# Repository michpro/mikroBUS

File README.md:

# mikroBUS™ Add-on Boards Collection

This repository contains a collection of add-on boards designed according to the mikroBUS™ standard. These boards can be used with any microcontroller platform that supports the mikroBUS™ socket, providing an easy way to expand the functionality of your projects.

* [**BluePill Base Board with 3 MikroBUS Sockets**](/BluePill_base/README.md)
* [**Arduino UNO Click Shield**](/Arduino_UNO_click_shield/README.md) -  SPI to UART firmware

---

* [**CAN Click**](/CAN_Click/README.md)
* [**Ethernet W5500 mini Click**](/ETH_W5500_mini_Click/README.md)
* [**HLW8032 Click - energy metering module**](/HLW8032_Click/README.md)
* [**I²C to 1-Wire Click**](/I2C_1-Wire_Click/README.md)
* [**I²C EEPROM/FRAM Click**](/I2C_EEPROM_Click/README.md)
* [**LIN Click**](/LIN_Click/README.md)
* [**LoRa Click**](/LoRa_Click/README.md)
* [**OpenTherm Click**](/OpenTherm_Click/README.md)
* [**RS485 Click**](/RS485_Click/README.md)
* [**UI Click with SCT-013 interface**](/SCT-013_UI_Click/README.md)

## **Reporting bugs**

[Create an issue on GitHub](https://github.com/michpro/mikroBUS/issues)

---

## **License**

Copyright © 2023-2025 Michal Protasowicki

This project is released under CERN Open Hardware Licence Version 2 - Permissive.

The software parts of the project are available under the MIT licence.

---

## **Support**
If You find my projects interesting and You wanted to support my work, You can give me a cup of coffee or a keg of beer :)

&nbsp;&nbsp;&nbsp;&nbsp;&nbsp;&nbsp;&nbsp;&nbsp;&nbsp;&nbsp;

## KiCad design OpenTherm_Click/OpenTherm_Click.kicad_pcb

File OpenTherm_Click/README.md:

# **OpenTherm Click**

- [**OpenTherm Click**](#opentherm-click)
  - [**Overview**](#overview)
    - [**Features**](#features)
  - [**Schematic diagram**](#schematic-diagram)
  - [**Module visualisation**](#module-visualisation)
  - [**Assembly**](#assembly)
  - [**Production files**](#production-files)
  - [**Testing out the hardware**](#testing-out-the-hardware)
    - [Prerequisites](#prerequisites)
    - [Instructions](#instructions)
    - [Notes](#notes)
  - [**Software**](#software)
  - [**Reporting bugs**](#reporting-bugs)
  - [**License**](#license)
    - [**Hardware**](#hardware)
    - [**Software**](#software-1)
  - [**Support**](#support)

---

## **Overview**
The OpenTherm Click is a compact module designed to interface with OpenTherm-compatible heating systems, such as boilers and thermostats. It facilitates communication using the OpenTherm protocol, incorporating electrical isolation for safety and compatibility.

### **Features**
* OpenTherm slave interface to communicate with a boiler
* OpenTherm master interface to communicate with a thermostat
* can implement master, slave and gateway modes
* built-in (3.3-5V) to 24V DC-DC step up converter
* Compact Design - optimized for integration with microcontroller systems, such as mikroBUS™ Click boards.

This work is based on [otgw.tclcode.com](https://otgw.tclcode.com) project.

---

## **Schematic diagram**

## **Module visualisation**
(click on the image to see the 3D model)
<p align="center"></p>

## **Assembly**
[Interactive BOM and placement](https://michpro.github.io/mikroBUS/OpenTherm_Click/docs/ibom.html)

## **Production files**
Production files can be found [**here**](./production/).

---
## **Testing out the hardware**
Below are the start-up instructions for the [click_test.ino](./software/click_test/click_test.ino) Arduino program, a diagnostic tool designed to test and validate the electrical and communication integrity between a boiler and thermostat circuits on the OpenTherm Click. These instructions guide you through the process step-by-step, ensuring you can verify your hardware setup correctly.

### Prerequisites
- **OpenTherm Click**: Ensure it is properly connected to base µC module.
- **Computer**: Equipped with Arduino IDE or a serial monitor software.
- **Multimeter**: Required for measuring voltages and currents.
- **Two Wires**: Needed to connect the BOILER and THERM terminals during testing.

### Instructions

1. **Upload the Program**
   - Load the [click_test.ino](./software/click_test/click_test.ino) program onto your Arduino board using the Arduino IDE.<br>
    *If necessary, adjust the pins used in the programme.*

2. **Open Serial Monitor**
   - Launch the serial monitor in the Arduino IDE or your preferred serial terminal software.
   - Set the baud rate to **115200**.

3. **Initial Setup**
   - Disconnect the 'THERM' and 'BOILER' terminals from each other if they are connected.
   - Check the LEDs on the Click:
     - **'PWR'** and **'RxT'** LEDs should be lit.
     - **'RxB'** LED should be off.
   - The serial monitor will display a prompt. If the LED statuses match, type **`y`** and press Enter to proceed.

4. **Voltage Measurement 1**
   - Use a multimeter to measure the voltage between the **+24V test point** and **GND**.
   - Expected range: **23.5V to 24.5V**.
   - If within range, type **`y`** in the serial monitor to proceed.

5. **Voltage Measurement 2**
   - Measure the voltage between the **T+ test point** and **GND**.
   - Expected value: Approximately **24V**.
   - If correct, type **`y`** to proceed.

6. **Current Measurement 1**
   - Measure the current flowing between **T+** and **GND**.
   - Expected range: **5mA to 9mA**.
   - Verify that the **RxT LED** is **not lit** during this measurement.
   - If correct, type **`y`** to proceed.

7. **Activate MASTER-OUT and Current Measurement 2**
   - The program will activate the 'MASTER-OUT' line (you’ll see a message in the serial monitor).
   - Measure the current between **T+** and **GND** again.
   - Expected range: **17mA to 23mA**.
   - Ensure the **RxT LED** remains **not lit**.
   - If correct, type **`y`** to proceed.

8. **Connect Terminals and Voltage Measurement 3**
   - Connect the **BOILER** and **THERM** terminals using two wires (polarity does not matter).
   - Measure the voltage between test points **B1** and **B2**.
   - Expected range: **15V to 18V**.
   - If within range, type **`y`** to proceed.

9. **Check RxB LED**
   - The program will activate 'MASTER-OUT' again.
   - Observe the **'RxB' LED**; it should **light up**.
   - If it does, type **`y`** to proceed.

10. **Activate SLAVE-OUT and Voltage Measurement 4**
    - The program will activate the 'SLAVE-OUT' line.
    - Check that the **RxT LED** **stops lighting up**.
    - Measure the voltage between **B1** and **B2** again.
    - Expected range: **5V to 7V**.
    - If correct, type **`y`** to proceed.

11. **Test Result**
    - If all steps are completed successfully, the serial monitor will display:
      ```
      *****************
      *  TEST PASSED  *
      *****************
      ```
    - If any step fails, it will show:
      ```
      *****************
      * TEST FAIL !!! *
      *****************
      ```

12. **Continuous Testing (if passed)**
    - If the test passes, the program will enter a continuous testing mode.
    - It will repeatedly check communication between the boiler and thermostat, printing:
      - **"Boiler inbound, thermostat outbound ... OK"** or **"Failed"** with a reason.
      - **"Boiler outbound, thermostat inbound ... OK"** or **"Failed"** with a reason.

### Notes
- **Test Points and LEDs**: Ensure you correctly identify the test points (+24V, T+, GND, B1, B2) and LEDs (PWR, RxT, RxB) on the OpenTherm Click.
- **Safety**: Exercise caution when measuring voltages and currents to avoid short circuits.
- **Troubleshooting**: If a measurement falls outside the expected range:
  - Double-check your connections and multimeter settings.
  - Retry the step. Persistent issues may indicate a problem with the Click or setup.

<br>

***Follow these instructions carefully to test and validate your OpenTherm Click setup. Each step requires confirmation via the serial monitor, so keep it open and active throughout the process. Successful completion ensures your boiler and thermostat circuits are functioning correctly.***

---

## **Software**
- Recommended library for use in your OpenTherm projects: 
  [https://github.com/ihormelnyk/opentherm_library](https://github.com/ihormelnyk/opentherm_library)

---

## **Reporting bugs**

[Create an issue on GitHub](https://github.com/michpro/mikroBUS/issues)

---

## **License**
Copyright © 2025 Michal Protasowicki

### **Hardware**
  * Hardware part of this project is released under CERN Open Hardware Licence Version 2 - Permissive.

### **Software**
  * Software part of this project is released under MIT Licence.

---

## **Support**
If You find my projects interesting and You wanted to support my work, You can give me a cup of coffee or a keg of beer :)

&nbsp;&nbsp;&nbsp;&nbsp;&nbsp;&nbsp;&nbsp;&nbsp;&nbsp;&nbsp;

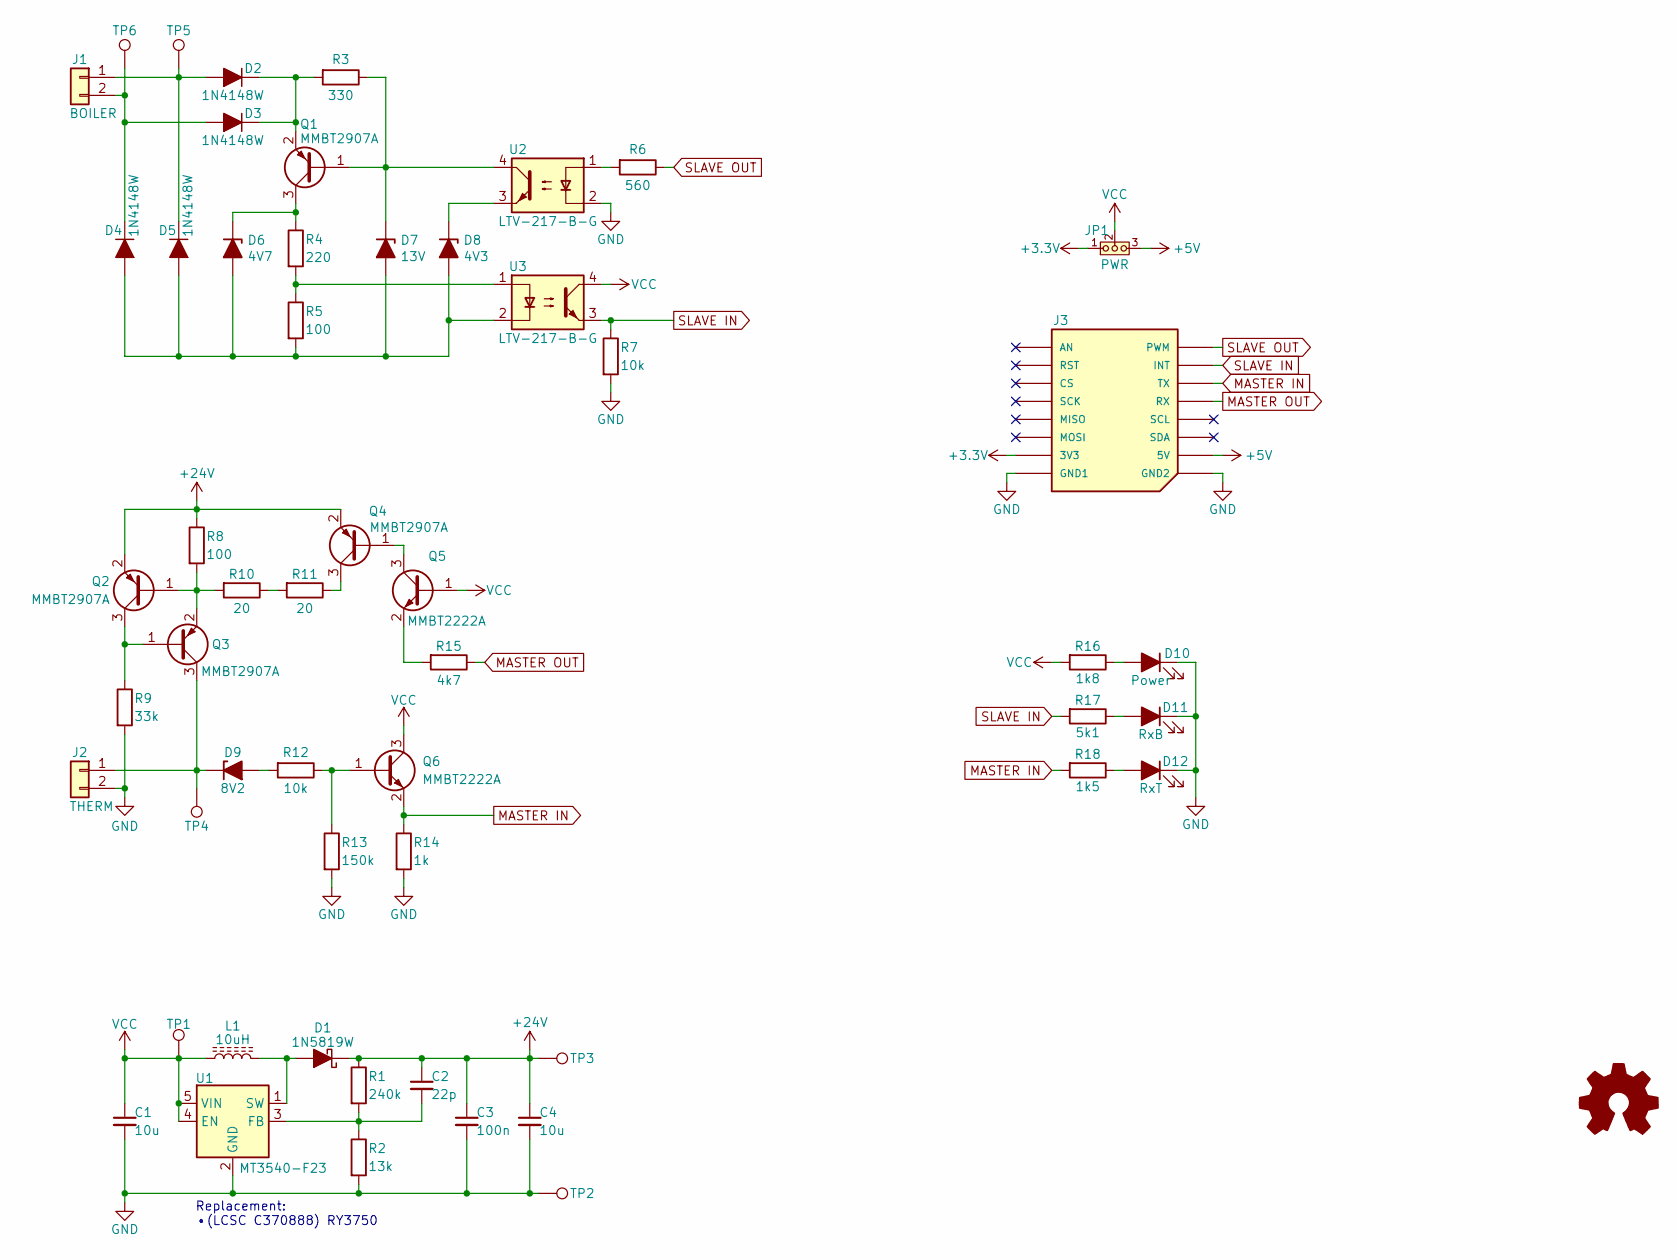
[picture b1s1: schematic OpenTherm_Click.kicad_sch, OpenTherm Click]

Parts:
C1: 10u; C_0603_1608Metric; LCSC C19702
C2: 22p; C_0603_1608Metric; LCSC C1653
C3: 100n; C_0603_1608Metric; LCSC C14663
C4: 10u; C_0805_2012Metric; LCSC C440198
D1: 1N5819W; D_SOD-123; LCSC C8598
D2, D3, D4, D5: 1N4148W; D_SOD-123; LCSC C7420318
D6: 4V7; D_SOD-123; LCSC C19077400
D7: 13V; D_SOD-123; LCSC C22399883
D8: 4V3; D_SOD-123; LCSC C19077399
D9: 8V2; D_SOD-123; LCSC C22399882
D10: Power; LED_0805_2012Metric; LCSC C84256
D11: RxB; LED_0805_2012Metric; LCSC C2297
D12: RxT; LED_0805_2012Metric; LCSC C2296
J1: BOILER; Altech_AK100_1x02_P5.00mm; LCSC ------
J2: THERM; Altech_AK100_1x02_P5.00mm; LCSC ------
J3: OpenTherm Click v${REVISION} by MPro; mikroBUS_module_L; LCSC -----
JP1: PWR; PinHeader_1x03_P2.54mm_Vertical; LCSC C5383112
L1: 10uH; Inductor_4.2x4.4mm; LCSC C177242
LOGO1: Logo_Open_Hardware_Small; OSHW-Logo2_7.3x6mm_SilkScreen
Q1, Q2, Q3, Q4: MMBT2907A; SOT-23; LCSC C7420352
Q5, Q6: MMBT2222A; SOT-23; LCSC C8512
R1: 240k; R_0603_1608Metric; LCSC C4197
R2: 13k; R_0603_1608Metric; LCSC C22797
R3: 330; R_0603_1608Metric; LCSC C23138
R4: 220; R_0603_1608Metric; LCSC C22962
R5, R8: 100; R_0603_1608Metric; LCSC C22775
R6: 560; R_0603_1608Metric; LCSC C23204
R7, R12: 10k; R_0603_1608Metric; LCSC C25804
R9: 33k; R_0603_1608Metric; LCSC C4216
R10, R11: 20; R_0603_1608Metric; LCSC C22950
R13: 150k; R_0603_1608Metric; LCSC C22807
R14: 1k; R_0603_1608Metric; LCSC C21190
R15: 4k7; R_0603_1608Metric; LCSC C23162
R16: 1k8; R_0603_1608Metric; LCSC C4177
R17: 5k1; R_0603_1608Metric; LCSC C23186
R18: 1k5; R_0603_1608Metric; LCSC C22843
TP1: VCC; TestPoint_Pad_D2.0mm; LCSC ------
TP2: GND; TestPoint_Pad_D2.0mm; LCSC ------
TP3: +24V; TestPoint_Pad_D2.0mm; LCSC ------
TP4: T+; TestPoint_Pad_D2.0mm; LCSC ------
TP5: B1; TestPoint_Pad_D2.0mm; LCSC ------
TP6: B2; TestPoint_Pad_D2.0mm; LCSC ------
U1: MT3540-F23; SOT-23-5; LCSC C181783
U2, U3: LTV-217-B-G; SOP-4_4.4x2.6mm_P1.27mm; LCSC C115450

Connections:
+3.3V: J3.P7 (3V3), JP1.1 (A)
+5V: J3.P10 (5V), JP1.3 (B)
+24V: C2.1, C3.1, C4.1, D1.1 (K), Q2.2 (E), Q4.2 (E), R1.1, R8.1, TP3.1
GND: C1.2, C3.2, C4.2, D10.1 (K), D11.1 (K), D12.1 (K), J2.2, J3.P8 (GND1), J3.P9 (GND2), R2.2, R7.2, R9.2, R13.2, R14.2, TP2.1, U1.2 (GND), U2.2
MASTER IN: J3.P14 (TX), Q6.2 (E), R14.1, R18.2
MASTER OUT: J3.P13 (RX), R15.1
unnamed: D1.2 (A), L1.2, U1.1 (SW)
unnamed: D2.2 (A), D5.1 (K), J1.1, TP5.1
unnamed: D2.1 (K), D3.1 (K), Q1.2 (E), R3.2
unnamed: D3.2 (A), D4.1 (K), J1.2, TP6.1
unnamed: D4.2 (A), D5.2 (A), D6.2 (A), D7.2 (A), D8.2 (A), R5.2, U3.2
unnamed: D6.1 (K), Q1.3 (C), R4.1
unnamed: D7.1 (K), Q1.1 (B), R3.1, U2.4
unnamed: D8.1 (K), U2.3
unnamed: D9.2 (A), R12.2
unnamed: D9.1 (K), J2.1, Q3.3 (C), TP4.1
unnamed: D10.2 (A), R16.1
unnamed: D11.2 (A), R17.1
unnamed: D12.2 (A), R18.1
unnamed: Q2.1 (B), Q3.2 (E), R8.2, R10.2
unnamed: Q2.3 (C), Q3.1 (B), R9.1
unnamed: Q4.1 (B), Q5.3 (C)
unnamed: Q4.3 (C), R11.1
unnamed: Q5.2 (E), R15.2
unnamed: Q6.1 (B), R12.1, R13.1
unnamed: R4.2, R5.1, U3.1
unnamed: R6.2, U2.1
unnamed: R10.1, R11.2
unnamed: C2.2, R1.2, R2.1, U1.3 (FB)
SLAVE IN: J3.P15 (INT), R7.1, R17.2, U3.3
SLAVE OUT: J3.P16 (PWM), R6.1
VCC: C1.1, JP1.2 (C), L1.1, Q5.1 (B), Q6.3 (C), R16.2, TP1.1, U1.4 (EN), U1.5 (VIN), U3.4

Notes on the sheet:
Replacement: •(LCSC C370888) RY3750

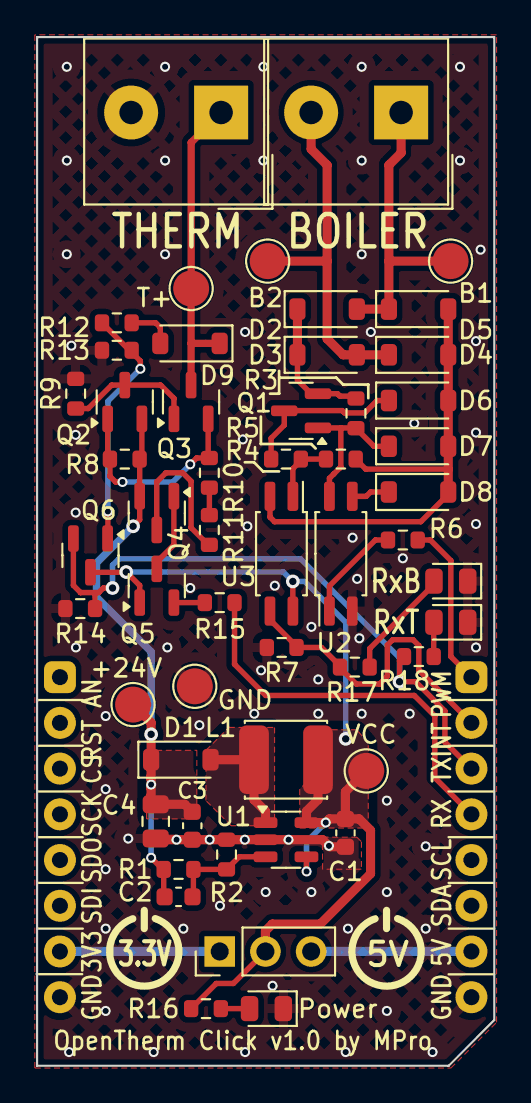
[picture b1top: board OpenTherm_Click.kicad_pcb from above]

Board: 2 copper layers, 25.4 x 57.2 mm, 55 parts (1 on the bottom side), 32 nets.

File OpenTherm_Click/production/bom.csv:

Designator,Footprint,Quantity,Value,LCSC Part #
C1,0603,1,10u,C19702
C2,0603,1,22p,C1653
C3,0603,1,100n,C14663
C4,0805,1,10u,C440198
D1,D_SOD-123,1,1N5819W,C8598
D10,0805,1,Power,C84256
D11,0805,1,RxB,C2297
D12,0805,1,RxT,C2296
"D2, D3, D4, D5",D_SOD-123,4,1N4148W,C7420318
D6,D_SOD-123,1,4V7,C19077400
D7,D_SOD-123,1,13V,C22399883
D8,D_SOD-123,1,4V3,C19077399
D9,D_SOD-123,1,8V2,C22399882
JP1,PinHeader_1x03_P2.54mm_Vertical,1,PWR,C5383112
L1,Inductor_4.2x4.4mm,1,10uH,C177242
"Q1, Q2, Q3, Q4",SOT-23,4,MMBT2907A,C7420352
"Q5, Q6",SOT-23,2,MMBT2222A,C8512
R1,0603,1,240k,C4197
"R10, R11",0603,2,20,C22950
"R12, R7",0603,2,10k,C25804
R13,0603,1,150k,C22807
R14,0603,1,1k,C21190
R15,0603,1,4k7,C23162
R16,0603,1,1k8,C4177
R17,0603,1,5k1,C23186
R18,0603,1,1k5,C22843
R2,0603,1,13k,C22797
R3,0603,1,330,C23138
R4,0603,1,220,C22962
"R5, R8",0603,2,100,C22775
R6,0603,1,560,C23204
R9,0603,1,33k,C4216
U1,SOT-23-5,1,MT3540-F23,C181783
"U2, U3",SOP-4_4.4x2.6mm_P1.27mm,2,LTV-217-B-G,C115450

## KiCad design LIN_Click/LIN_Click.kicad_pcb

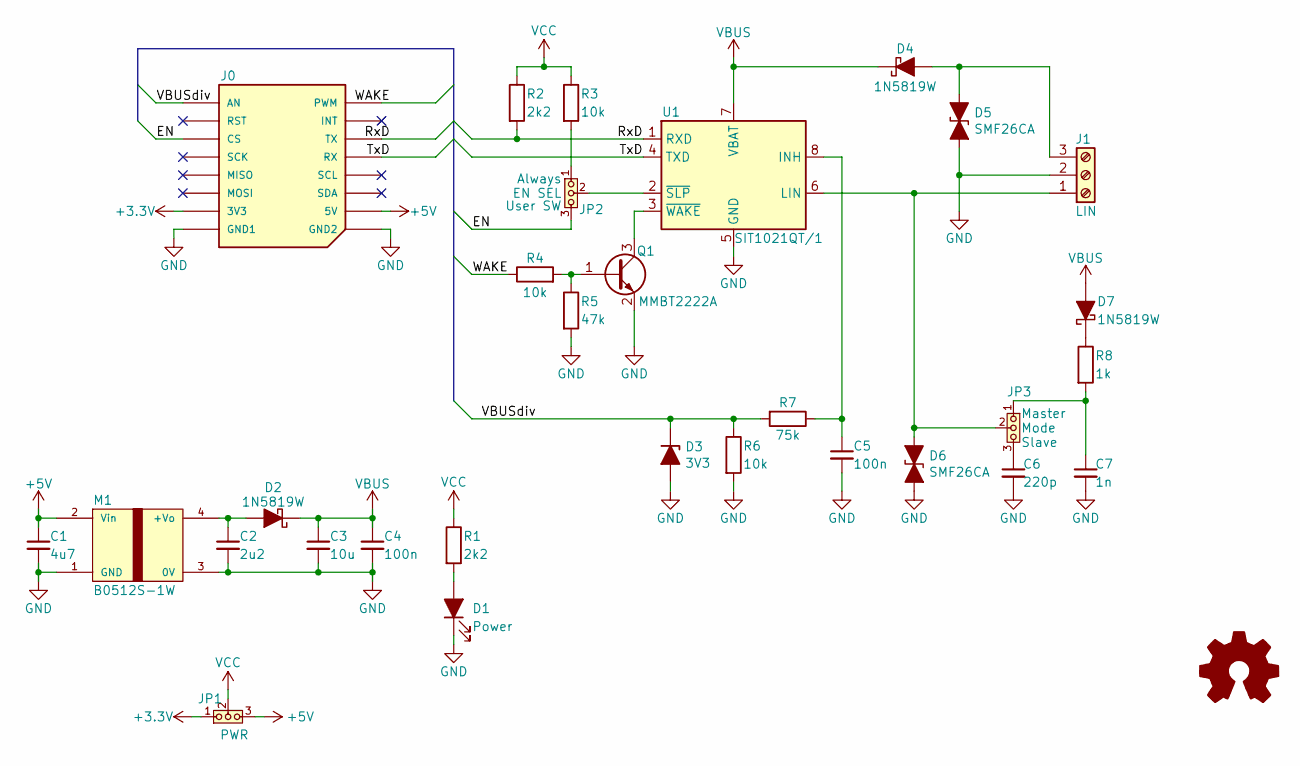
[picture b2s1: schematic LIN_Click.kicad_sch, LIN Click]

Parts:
C1: 4u7; C_0805_2012Metric; LCSC C1779
C2: 2u2; C_0805_2012Metric; LCSC C377773
C3: 10u; C_0805_2012Metric; LCSC C440198
C4, C5: 100n; C_0805_2012Metric; LCSC C49678
C6: 220p; C_0805_2012Metric; LCSC C107145
C7: 1n; C_0805_2012Metric; LCSC C46653
D1: Power; LED_0805_2012Metric; LCSC C2296
D2, D4, D7: 1N5819W; D_SOD-123; LCSC C8598
D3: 3V3; D_SOD-123; LCSC C19077392
D5, D6: SMF26CA; D_SOD-123FL; LCSC C19077516
J0: LIN Click v${REVISION} by MPro; mikroBUS_module_M; LCSC -----
J1: LIN; DG250-3.5-03P-11-00AH; LCSC -----
JP1: PWR; PinHeader_1x03_P2.54mm_Vertical; LCSC C5383112
JP2: EN SEL; PinHeader_1x03_P2.54mm_Vertical; LCSC C5383112
JP3: Mode; PinHeader_1x03_P2.54mm_Vertical; LCSC C5383112
LOGO1: Logo_Open_Hardware_Small; OSHW-Logo2_7.3x6mm_SilkScreen
M1: B0512S-1W; BxxyyS-1W; LCSC C3031179
Q1: MMBT2222A; SOT-23; LCSC C8512
R1, R2: 2k2; R_0805_2012Metric; LCSC C17520
R3, R4, R6: 10k; R_0805_2012Metric; LCSC C17414
R5: 47k; R_0805_2012Metric; LCSC C17713
R7: 75k; R_0805_2012Metric; LCSC C17819
R8: 1k; R_0805_2012Metric; LCSC C17513
U1: SIT1021QT/1; SO-8_3.9x4.9mm_P1.27mm; LCSC C7433978

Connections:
+3.3V: J0.P7 (3V3), JP1.1 (A)
+5V: C1.1, J0.P10 (5V), JP1.3 (B), M1.2 (Vin)
/EN: J0.P3 (CS), JP2.3 (B)
/RxD: J0.P14 (TX), R2.2, U1.1 (RXD)
/TxD: J0.P13 (RX), U1.4 (TXD)
/VBUSdiv: D3.1 (K), J0.P1 (AN), R6.1, R7.2
/WAKE: J0.P16 (PWM), R4.1
GND: C1.2, C2.2, C3.2, C4.2, C5.2, C6.2, C7.2, D1.1 (K), D3.2 (A), D5.2 (A2), D6.2 (A2), J0.P8 (GND1), J0.P9 (GND2), J1.2, M1.1 (GND), M1.3 (0V), Q1.2 (E), R5.2, R6.2, U1.5 (GND)
unnamed: D1.2 (A), R1.2
unnamed: C2.1, D2.2 (A), M1.4 (+Vo)
unnamed: D4.2 (A), D5.1 (A1), J1.3
unnamed: D6.1 (A1), J1.1, JP3.2 (C), U1.6 (LIN)
unnamed: D7.1 (K), R8.1
unnamed: JP2.1 (A), R3.2
unnamed: JP2.2 (C), U1.2 (~SLP)
unnamed: C7.1, JP3.1 (A), R8.2
unnamed: C6.1, JP3.3 (B)
unnamed: Q1.1 (B), R4.2, R5.1
unnamed: Q1.3 (C), U1.3 (~WAKE)
unnamed: C5.1, R7.1, U1.8 (INH)
VBUS: C3.1, C4.1, D2.1 (K), D4.1 (K), D7.2 (A), U1.7 (VBAT)
VCC: JP1.2 (C), R1.1, R2.1, R3.1

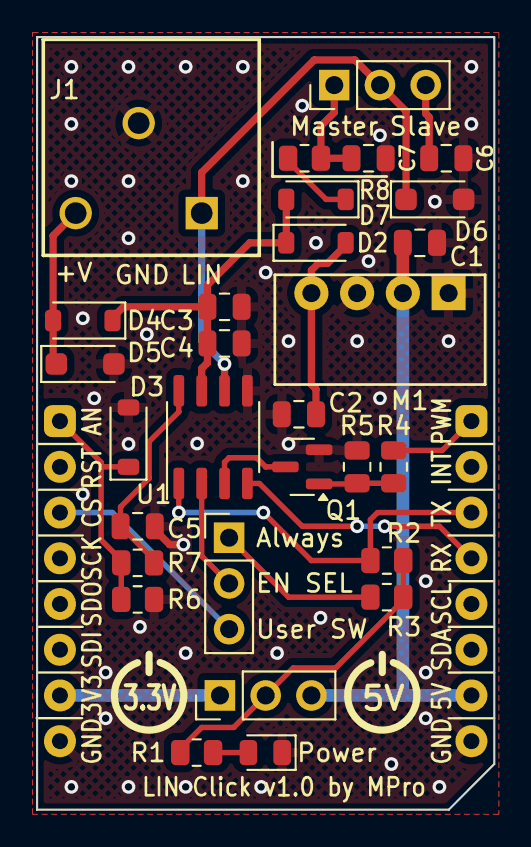
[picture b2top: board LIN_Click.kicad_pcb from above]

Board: 2 copper layers, 25.4 x 42.9 mm, 31 parts (1 on the bottom side), 22 nets.

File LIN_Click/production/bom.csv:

Designator,Footprint,Quantity,Value,LCSC Part #
C1,0805,1,4u7,C1779
C2,0805,1,2u2,C377773
C3,0805,1,10u,C440198
"C4, C5",0805,2,100n,C49678
C6,0805,1,220p,C107145
C7,0805,1,1n,C46653
D1,0805,1,Power,C2296
"D2, D4, D7",D_SOD-123,3,1N5819W,C8598
D3,D_SOD-123,1,3V3,C19077392
"D5, D6",D_SOD-123FL,2,SMF26CA,C19077516
J1,DG250-3.5-03P-11-00AH,1,LIN,-----
JP1,PinHeader_1x03_P2.54mm_Vertical,1,PWR,C5383112
JP2,PinHeader_1x03_P2.54mm_Vertical,1,EN SEL,C5383112
JP3,PinHeader_1x03_P2.54mm_Vertical,1,Mode,C5383112
M1,BxxyyS-1W,1,B0512S-1W,C3031179
Q1,SOT-23,1,MMBT2222A,C8512
"R1, R2",0805,2,2k2,C17520
"R3, R4, R6",0805,3,10k,C17414
R5,0805,1,47k,C17713
R7,0805,1,75k,C17819
R8,0805,1,1k,C17513
U1,SO-8_3.9x4.9mm_P1.27mm,1,SIT1021QT/1,C7433978

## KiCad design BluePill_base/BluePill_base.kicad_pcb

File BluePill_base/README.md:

# **BluePill Base Board with 3 MikroBUS™ Sockets**

- [**BluePill Base Board with 3 MikroBUS™ Sockets**](#bluepill-base-board-with-3-mikrobus-sockets)
  - [**Overview**](#overview)
    - [**Supported boards**](#supported-boards)
    - [**Features**](#features)
  - [**Detailed Description**](#detailed-description)
    - [**Microcontroller Connection**](#microcontroller-connection)
    - [**MikroBUS™ Sockets**](#mikrobus-sockets)
    - [**Communication Interfaces**](#communication-interfaces)
    - [**Configuration Jumpers**](#configuration-jumpers)
  - [**Schematic diagram**](#schematic-diagram)
  - [**Module visualisation**](#module-visualisation)
  - [**Assembly**](#assembly)
  - [**Production files**](#production-files)
  - [**Programming and Operation:**](#programming-and-operation)
  - [**Reporting bugs**](#reporting-bugs)
  - [**License**](#license)
  - [**Support**](#support)

---

## **Overview**
The BluePill Base Board is a versatile platform designed to extend the functionality of the BluePill microcontroller development board. This base board enhances the BluePill's capabilities by incorporating three MikroBUS™ sockets, enabling seamless integration of various MikroBUS™-compatible add-on modules such as sensors, communication interfaces, and other peripherals. It is an ideal solution for prototyping and developing embedded systems and IoT applications.

### **Supported boards**
  * **Standard BluePill** boards and clones with STM32F103 or STM32F072 µC
  * **BluePill Plus** with GD32F303CCT6 ARM M4F µC - [https://github.com/WeActStudio/BluePill-Plus](https://github.com/WeActStudio/BluePill-Plus)
  * **BluePill Plus CH32** with CH32V103C8T6 or CH32V203C8T6 RISV-V µC - [https://github.com/WeActStudio/WeActStudio.BluePill-Plus-CH32](https://github.com/WeActStudio/WeActStudio.BluePill-Plus-CH32)

### **Features**
* **Power Supply**:
  * Input via a standard barrel jack connector with reverse polarity protection.
  * Battery input for RTC clock via JST XH connector, with recharge option.
  * Power switch controlled by a P-channel MOSFET (*External power supply priority over USB for the +5V line*).
* **Voltage Regulation**:
  * 3.3V linear regulator (AMS1117-3.3) for the microcontroller and peripherals.
  * 5V power rail available for additional components and MikroBUS™ modules.
* **Connectors**:
  * Socket for the BluePill microcontroller board.
  * Three MikroBUS™ sockets for add-on modules.
  * UART header for serial communication (PA9/PA10 shared with the first MikroBUS™ socket).
  * CAN bus terminal block (PA11/PA12 shared with USB on the BluePill board).
* **Communication Interfaces**:
  * SPI, I²C, UART, and PWM support via MikroBUS™ sockets.
  * CAN bus interface using the SN65HVD230 transceiver.

---

## **Detailed Description**

### **Microcontroller Connection**
* **Socket**: The BluePill board connects via a 2x20 pin socket (M1), providing access to power (3.3V, 5V, GND) and all I/O pins.
* **Pin Mapping**: The socket interfaces with MikroBUS™ sockets and other peripherals, with specific pins allocated for SPI, I2C, UART, and CAN communication.<br>
<center>

  | Name | Socket 1 | Socket 2 | Socket 3 | Board | Notes |
  | :--- | :------: | :------: | :------: | :---: | :---- |
  | AN     | PA0  | PA4  | PB0  | | SPI0 NSS output Disabled (PA4) |
  | RST    | PB8  | PB14 | PB12 | | |
  | CS     | PB9  | PB15 | PB13 | | |
  | SCK    | PA5  | PA5  | PA5  | | |
  | MISO   | PA6  | PA6  | PA6  | | |
  | MOSI   | PA7  | PA7  | PA7  | | |
  | PWM    | PA8  | PA1  | PB1  | | |
  | INT    | PB5  | PB4  | PB3  | | JTAG-DP must be Disabled (PB3 & PB4) |
  | RX     | PA10 | PA3  | PB11 | PA10 | Shared between Board and Socket 1 |
  | TX     | PA9  | PA2  | PB10 | PA9  | Shared between Board and Socket 1 |
  | SCL    | PB6  | PB6  | PB6  | | |
  | SDA    | PB7  | PB7  | PB7  | | |
  | CAN Tx |      |      |      | PA12 | Shared with BluePill USB- |
  | CAN Rx |      |      |      | PA11 | Shared with BluePill USB+ |
  | CAN EN |      |      |      | PA15 | JTAG-DP must be Disabled |

</center>

### **MikroBUS™ Sockets**
* **Configuration**: Three MikroBUS™ sockets (J1, J2, J3) are implemented using dual 1x8 pin headers, adhering to the MikroBUS™ standard.
* **Pinout**:
  * **Power**: +3.3V, +5V, GND
  * **SPI**: MOSI, MISO, SCK, CS
  * **I2C**: SDA, SCL
  * **UART**: TX, RX
  * **Other**: PWM, Analog Input (AN), Interrupt (INT), Reset (RST)
* **Usage**: Each socket supports independent module connections, with signals routed to the BluePill's corresponding pins.

### **Communication Interfaces**
* **SPI**: Shared across MikroBUS™ sockets with individual chip select (CS) lines (CS1, CS2, CS3).
* **I2C**: SDA and SCL lines connected to the BluePill, configurable via jumpers (JP5, JP6).
* **UART**: Accessible via a 3-pin header (J7) and MikroBUS™ sockets (TX1/RX1, TX2/RX2, TX3/RX3).
* **CAN Bus**: Implemented with the SN65HVD230 transceiver (U3), connected to a 3-pin terminal block (J4) for CANH and CANL lines.
* **PWM**: Available on MikroBUS™ sockets (PWM1, PWM2, PWM3).

### **Configuration Jumpers**
* **JP1**: [Charge] If shorted, it supplies a small current through D2 and R5 to recharge the RTC clock battery/supercapacitor.
* **JP2**: [TERM] If shorted, it terminates the CAN bus with a 120Ω resistor..
* **JP3**: [CAN Tx] If shorted, it transmits the CAN Tx signal to the SN65HVD230 transceiver.
* **JP4**: [CAN Rx] If shorted, it transmits the CAN Rx signal from the SN65HVD230 transceiver.
* **JP5**: [SCL] If shorted, connects a pull-up resistor for the I²C bus to the line.
* **JP6**: [SDA] If shorted, connects a pull-up resistor for the I²C bus to the line.

---

## **Schematic diagram**

## **Module visualisation**
(click on the image to see the 3D model)
<p align="center"></p>

## **Assembly**
[Interactive BOM and placement](https://michpro.github.io/mikroBUS/BluePill_base/docs/ibom.html)

## **Production files**
Production files can be found [**here**](./production/).

## **Programming and Operation:**
  * Program the BluePill using an external programmer (e.g., via SWD pins).
  * Utilize the MikroBUS™ modules and UART/CAN interfaces as required.

---

## **Reporting bugs**

[Create an issue on GitHub](https://github.com/michpro/mikroBUS/issues)

---

## **License**
Copyright © 2025 Michal Protasowicki

This project is released under CERN Open Hardware Licence Version 2 - Permissive.

---

## **Support**
If You find my projects interesting and You wanted to support my work, You can give me a cup of coffee or a keg of beer :)

&nbsp;&nbsp;&nbsp;&nbsp;&nbsp;&nbsp;&nbsp;&nbsp;&nbsp;&nbsp;

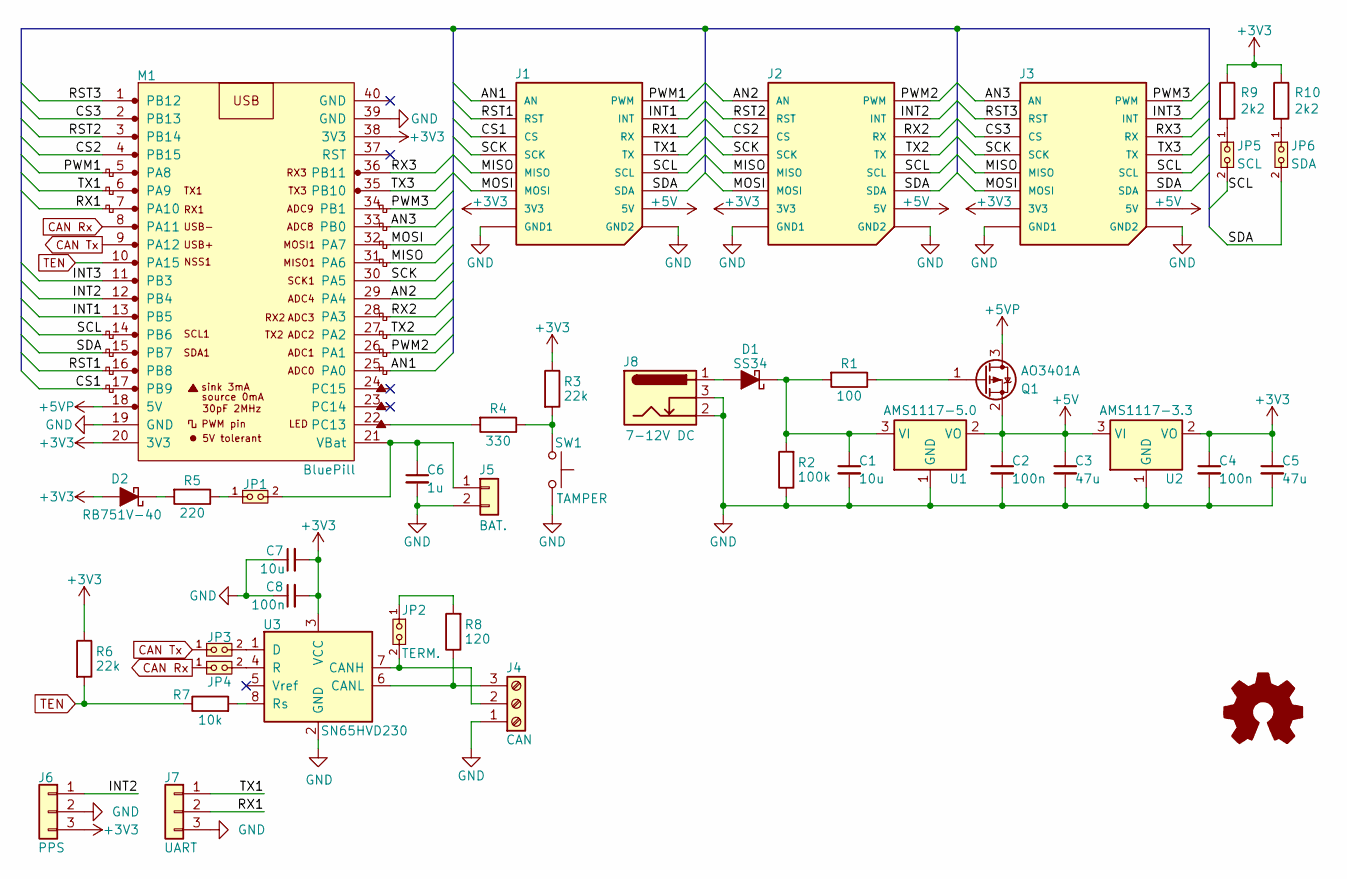
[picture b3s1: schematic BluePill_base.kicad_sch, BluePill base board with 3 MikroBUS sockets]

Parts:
C1, C7: 10u; C_0805_2012Metric; LCSC C440198
C2, C4, C8: 100n; C_0805_2012Metric; LCSC C49678
C3, C5: 47u; C_0805_2012Metric; LCSC C16780
C6: 1u; C_0805_2012Metric; LCSC C28323
D1: SS34; D_SMA; LCSC C8678
D2: RB751V-40; D_SOD-323; LCSC C7502691
J1, J2, J3: mikroBUS host connector; mikroBUS_host_connector; LCSC -----
J4: CAN; DG250-3.5-03P-11-00AH; LCSC -----
J5: BAT.; JST_XH_B2B-XH-A_1x02_P2.50mm_Vertical; LCSC C18077833
J6: PPS; PinHeader_1x03_P2.54mm_Vertical; LCSC C5383112
J7: UART; PinHeader_1x03_P2.54mm_Vertical; LCSC C5383112
J8: 7-12V DC; PJ-002A-SMT; LCSC C431534
JP1: Charge; PinHeader_1x02_P2.54mm_Vertical; LCSC C5383111
JP2: TERM.; PinHeader_1x02_P2.54mm_Vertical; LCSC C5383111
JP3: CAN Tx; PinHeader_1x02_P2.54mm_Vertical; LCSC C5383111
JP4: CAN Rx; PinHeader_1x02_P2.54mm_Vertical; LCSC C5383111
JP5: SCL; PinHeader_1x02_P2.54mm_Vertical; LCSC C27985187
JP6: SDA; PinHeader_1x02_P2.54mm_Vertical; LCSC C27985187
LOGO1: Logo_Open_Hardware_Small; OSHW-Logo2_7.3x6mm_SilkScreen
M1: BluePill; LCSC -----
Q1: AO3401A; SOT-23; LCSC C15127
R1: 100; R_0805_2012Metric; LCSC C17408
R2: 100k; R_0805_2012Metric; LCSC C149504
R3, R6: 22k; R_0805_2012Metric; LCSC C17560
R4: 330; R_0805_2012Metric; LCSC C17630
R5: 220; R_0805_2012Metric; LCSC C17557
R7: 10k; R_0805_2012Metric; LCSC C17414
R8: 120; R_0805_2012Metric; LCSC C17437
R9, R10: 2k2; R_0805_2012Metric; LCSC C17520
SW1: TAMPER; SW_Push_1P1T_NO_6x6mm_H9.5mm; LCSC C455118
U1: AMS1117-5.0; SOT-223-3_TabPin2; LCSC C6187
U2: AMS1117-3.3; SOT-223-3_TabPin2; LCSC C6186
U3: SN65HVD230; SOIC-8_3.9x4.9mm_P1.27mm; LCSC C12084

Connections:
+3V3: C4.1, C5.1, C7.2, C8.2, D2.2 (A), J1.P7 (3V3), J2.P7 (3V3), J3.P7 (3V3), J6.3, M1.20 (3V3), M1.38 (3V3), R3.1, R6.1, R9.1, R10.1, U2.2 (VO), U3.3 (VCC)
+5V: C2.1, C3.1, J1.P10 (5V), J2.P10 (5V), J3.P10 (5V), Q1.2 (S), U1.2 (VO), U2.3 (VI)
+5VP: M1.18 (5V), Q1.3 (D)
/AN1: J1.P1 (AN), M1.25 (PA0)
/AN2: J2.P1 (AN), M1.29 (PA4)
/AN3: J3.P1 (AN), M1.33 (PB0)
/CS1: J1.P3 (CS), M1.17 (PB9)
/CS2: J2.P3 (CS), M1.4 (PB15)
/CS3: J3.P3 (CS), M1.2 (PB13)
/INT1: J1.P15 (INT), M1.13 (PB5)
/INT2: J2.P15 (INT), J6.1, M1.12 (PB4)
/INT3: J3.P15 (INT), M1.11 (PB3)
/MISO: J1.P5 (MISO), J2.P5 (MISO), J3.P5 (MISO), M1.31 (PA6)
/MOSI: J1.P6 (MOSI), J2.P6 (MOSI), J3.P6 (MOSI), M1.32 (PA7)
/PWM1: J1.P16 (PWM), M1.5 (PA8)
/PWM2: J2.P16 (PWM), M1.26 (PA1)
/PWM3: J3.P16 (PWM), M1.34 (PB1)
/RST1: J1.P2 (RST), M1.16 (PB8)
/RST2: J2.P2 (RST), M1.3 (PB14)
/RST3: J3.P2 (RST), M1.1 (PB12)
/RX1: J1.P14 (RX), J7.2, M1.7 (PA10)
/RX2: J2.P14 (RX), M1.28 (PA3)
/RX3: J3.P14 (RX), M1.36 (PB11)
/SCK: J1.P4 (SCK), J2.P4 (SCK), J3.P4 (SCK), M1.30 (PA5)
/SCL: J1.P12 (SCL), J2.P12 (SCL), J3.P12 (SCL), JP5.2 (B), M1.14 (PB6)
/SDA: J1.P11 (SDA), J2.P11 (SDA), J3.P11 (SDA), JP6.2 (B), M1.15 (PB7)
/TX1: J1.P13 (TX), J7.1, M1.6 (PA9)
/TX2: J2.P13 (TX), M1.27 (PA2)
/TX3: J3.P13 (TX), M1.35 (PB10)
CAN Rx: JP4.1 (A), M1.8 (PA11)
CAN Tx: JP3.1 (A), M1.9 (PA12)
GND: C1.2, C2.2, C3.2, C4.2, C5.2, C6.2, C7.1, C8.1, J1.P8 (GND1), J1.P9 (GND2), J2.P8 (GND1), J2.P9 (GND2), J3.P8 (GND1), J3.P9 (GND2), J4.1, J5.2, J6.2, J7.3, J8.2, J8.3, M1.19 (GND), M1.39 (GND), R2.1, SW1.2, U1.1 (GND), U2.1 (GND), U3.2 (GND)
unnamed: D1.2 (A), J8.1
unnamed: C1.1, D1.1 (K), R1.2, R2.2, U1.3 (VI)
unnamed: D2.1 (K), R5.2
unnamed: J4.2, JP2.2 (B), U3.7 (CANH)
unnamed: J4.3, R8.1, U3.6 (CANL)
unnamed: C6.1, J5.1, JP1.2 (B), M1.21 (VBat)
unnamed: JP1.1 (A), R5.1
unnamed: JP2.1 (A), R8.2
unnamed: JP3.2 (B), U3.1 (D)
unnamed: JP4.2 (B), U3.4 (R)
unnamed: JP5.1 (A), R9.2
unnamed: JP6.1 (A), R10.2
unnamed: M1.22 (PC13), R4.2
unnamed: Q1.1 (G), R1.1
unnamed: R3.2, R4.1, SW1.1
unnamed: R7.2, U3.8 (Rs)
TEN: M1.10 (PA15), R6.2, R7.1

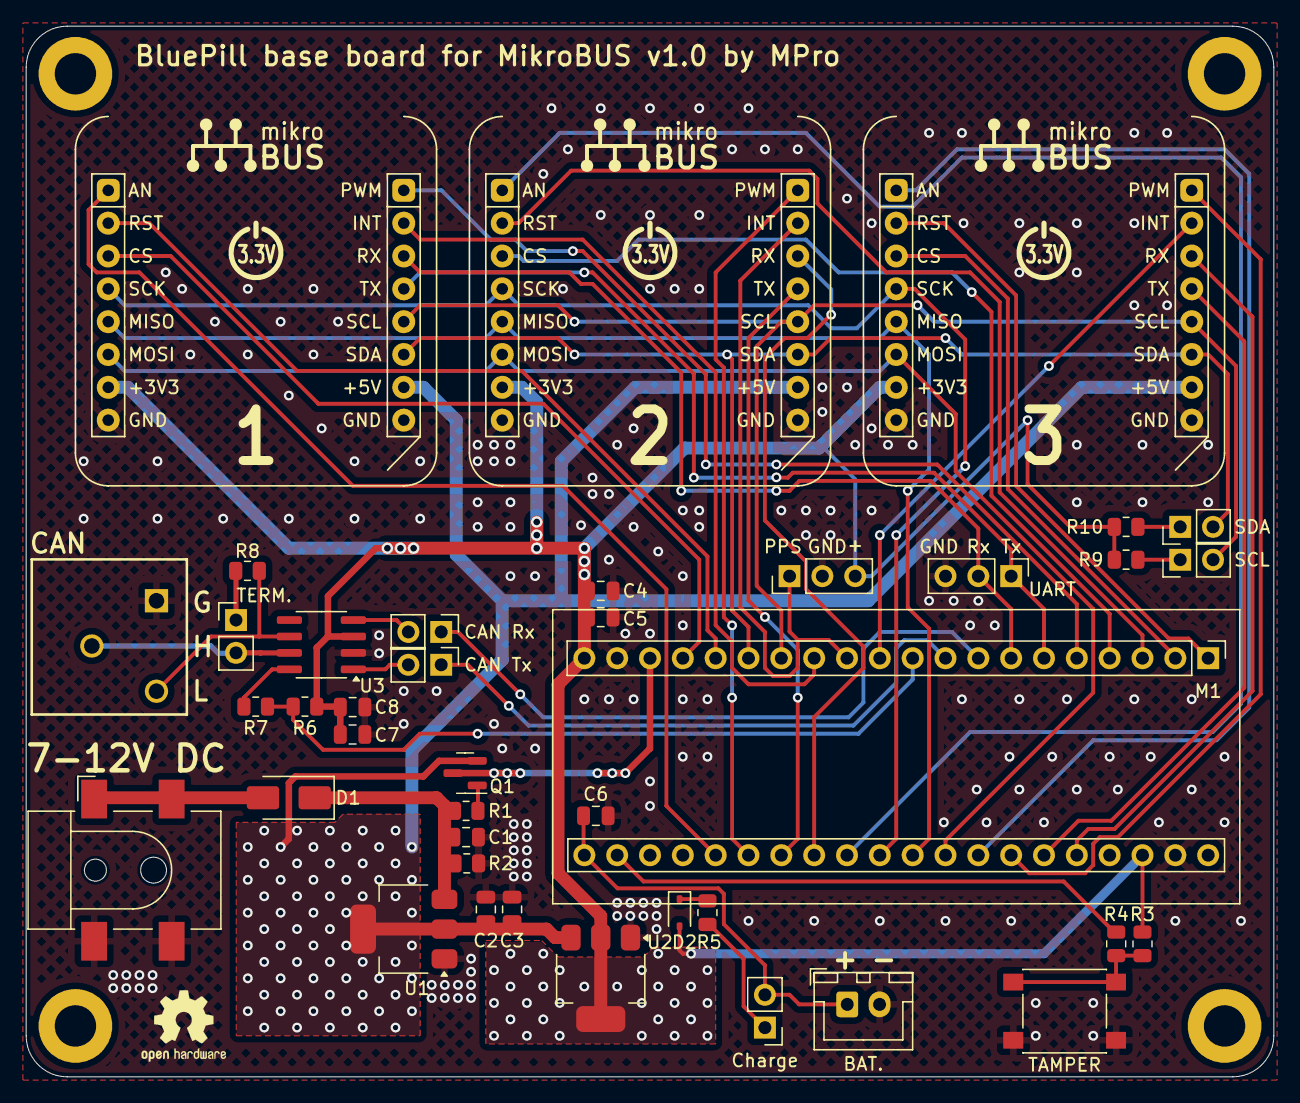
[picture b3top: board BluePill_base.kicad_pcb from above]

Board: 2 copper layers, 96.5 x 81.3 mm, 41 parts (0 on the bottom side), 49 nets.

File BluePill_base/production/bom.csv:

Designator,Footprint,Quantity,Value,LCSC Part #
"C1, C7",0805,2,10u,C440198
"C2, C4, C8",0805,3,100n,C49678
"C3, C5",0805,2,47u,C16780
C6,0805,1,1u,C28323
D1,D_SMA,1,SS34,C8678
D2,D_SOD-323,1,RB751V-40,C7502691
J5,JST_XH_B2B-XH-A_1x02_P2.50mm_Vertical,1,BAT.,C18077833
J6,PinHeader_1x03_P2.54mm_Vertical,1,PPS,C5383112
J7,PinHeader_1x03_P2.54mm_Vertical,1,UART,C5383112
J8,PJ-002A-SMT,1,7-12V DC,C431534
JP1,PinHeader_1x02_P2.54mm_Vertical,1,Charge,C5383111
JP2,PinHeader_1x02_P2.54mm_Vertical,1,TERM.,C5383111
JP3,PinHeader_1x02_P2.54mm_Vertical,1,CAN Tx,C5383111
JP4,PinHeader_1x02_P2.54mm_Vertical,1,CAN Rx,C5383111
JP5,PinHeader_1x02_P2.54mm_Vertical,1,SCL,C27985187
JP6,PinHeader_1x02_P2.54mm_Vertical,1,SDA,C27985187
Q1,SOT-23,1,AO3401A,C15127
R1,0805,1,100,C17408
"R10, R9",0805,2,2k2,C17520
R2,0805,1,100k,C149504
"R3, R6",0805,2,22k,C17560
R4,0805,1,330,C17630
R5,0805,1,220,C17557
R7,0805,1,10k,C17414
R8,0805,1,120,C17437
SW1,SW_Push_1P1T_NO_6x6mm_H9.5mm,1,TAMPER,C455118
U1,SOT-223-3_TabPin2,1,AMS1117-5.0,C6187
U2,SOT-223-3_TabPin2,1,AMS1117-3.3,C6186
U3,SOIC-8_3.9x4.9mm_P1.27mm,1,SN65HVD230,C12084

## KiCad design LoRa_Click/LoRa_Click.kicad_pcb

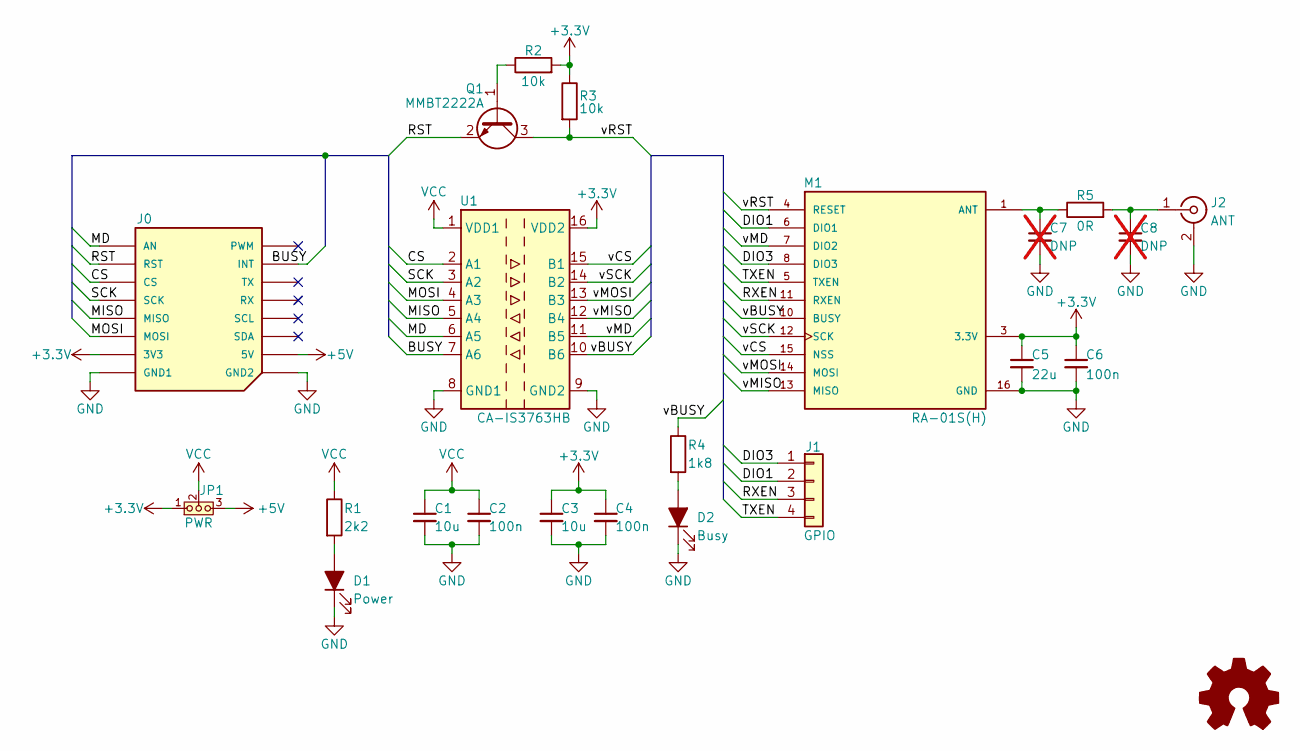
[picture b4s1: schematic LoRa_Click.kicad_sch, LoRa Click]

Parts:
C1, C3: 10u; C_0603_1608Metric; LCSC C19702
C2, C4, C6: 100n; C_0603_1608Metric; LCSC C14663
C5: 22u; C_0603_1608Metric; LCSC C59461
C7, C8: DNP; C_0603_1608Metric; LCSC -----; not fitted
D1: Power; LED_0603_1608Metric; LCSC C89811
D2: Busy; LED_0603_1608Metric; LCSC C2286
J0: LoRa Click v${REVISION} by MPro; mikroBUS_module_L; LCSC -----
J1: GPIO; PinHeader_1x04_P2.54mm_Vertical; LCSC C5383113
J2: ANT; SMA_Samtec_SMA-J-P-H-ST-EM1_EdgeMount; LCSC C496550
JP1: PWR; PinHeader_1x03_P2.54mm_Vertical; LCSC C5383112
LOGO1: Logo_Open_Hardware_Small; OSHW-Logo2_7.3x6mm_SilkScreen
M1: RA-01S(H); RA-01x; PARTREV V1.0; LCSC C724871
Q1: MMBT2222A; SOT-23; LCSC C8512
R1: 2k2; R_0603_1608Metric; LCSC C4190
R2, R3: 10k; R_0603_1608Metric; LCSC C25804
R4: 1k8; R_0603_1608Metric; LCSC C4177
R5: 0R; R_0603_1608Metric; LCSC C21189
U1: CA-IS3763HB; SSOP-16_3.9x4.9mm_P0.635mm; LCSC C5457088

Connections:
+3.3V: C3.1, C4.1, C5.1, C6.1, J0.P7 (3V3), JP1.1 (A), M1.3 (3.3V), R2.2, R3.1, U1.16 (VDD2)
+5V: J0.P10 (5V), JP1.3 (B)
/BUSY: J0.P15 (INT), U1.7 (A6)
/CS: J0.P3 (CS), U1.2 (A1)
/DIO1: J1.2, M1.6 (DIO1)
/DIO3: J1.1, M1.8 (DIO3)
/MD: J0.P1 (AN), U1.6 (A5)
/MISO: J0.P5 (MISO), U1.5 (A4)
/MOSI: J0.P6 (MOSI), U1.4 (A3)
/RST: J0.P2 (RST), Q1.2 (E)
/RXEN: J1.3, M1.11 (RXEN)
/SCK: J0.P4 (SCK), U1.3 (A2)
/TXEN: J1.4, M1.5 (TXEN)
/vBUSY: M1.10 (BUSY), R4.1, U1.10 (B6)
/vCS: M1.15 (NSS), U1.15 (B1)
/vMD: M1.7 (DIO2), U1.11 (B5)
/vMISO: M1.13 (MISO), U1.12 (B4)
/vMOSI: M1.14 (MOSI), U1.13 (B3)
/vRST: M1.4 (RESET), Q1.3 (C), R3.2
/vSCK: M1.12 (SCK), U1.14 (B2)
GND: C1.2, C2.2, C3.2, C4.2, C5.2, C6.2, C7.2, C8.2, D1.1 (K), D2.1 (K), J0.P8 (GND1), J0.P9 (GND2), J2.2 (Ext), M1.2 (GND), M1.9 (GND), M1.16 (GND), U1.8 (GND1), U1.9 (GND2)
unnamed: D1.2 (A), R1.2
unnamed: D2.2 (A), R4.2
unnamed: C8.1, J2.1 (In), R5.2
unnamed: C7.1, M1.1 (ANT), R5.1
unnamed: Q1.1 (B), R2.1
VCC: C1.1, C2.1, JP1.2 (C), R1.1, U1.1 (VDD1)

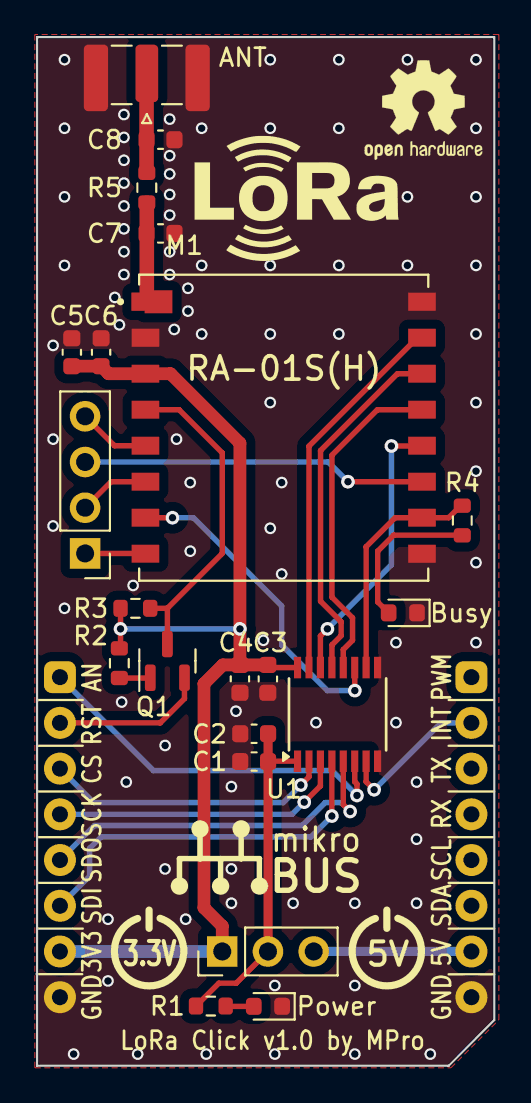
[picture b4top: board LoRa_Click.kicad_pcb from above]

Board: 2 copper layers, 25.4 x 57.1 mm, 23 parts (0 on the bottom side), 27 nets.

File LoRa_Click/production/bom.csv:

Designator,Footprint,Quantity,Value,LCSC Part #
"C1, C3",0603,2,10u,C19702
"C2, C4, C6",0603,3,100n,C14663
C5,0603,1,22u,C59461
D1,0603,1,Power,C89811
D2,0603,1,Busy,C2286
J1,PinHeader_1x04_P2.54mm_Vertical,1,GPIO,C5383113
J2,SMA_Samtec_SMA-J-P-H-ST-EM1_EdgeMount,1,ANT,C496550
JP1,PinHeader_1x03_P2.54mm_Vertical,1,PWR,C5383112
M1,RA-01x,1,RA-01S(H),C724871
Q1,SOT-23,1,MMBT2222A,C8512
R1,0603,1,2k2,C4190
"R2, R3",0603,2,10k,C25804
R4,0603,1,1k8,C4177
R5,0603,1,0R,C21189
U1,SSOP-16_3.9x4.9mm_P0.635mm,1,CA-IS3763HB,C5457088

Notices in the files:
OpenTherm_Click/software/click_test/click_test.ino:
\copyright SPDX-FileCopyrightText: Copyright 2025 Michal Protasowicki
\license SPDX-License-Identifier: MIT
Arduino_UNO_click_shield/Arduino_UNO_click_shield.kicad_pcb:
© 2023-2025 MPro
Licensed under CERN-OHL-P v2 or any later version
Arduino_UNO_click_shield/README.md:
License: CERN-OHL-P-2.0
License: MIT
BluePill_base/BluePill_base.kicad_pcb:
© 2025 MPro
